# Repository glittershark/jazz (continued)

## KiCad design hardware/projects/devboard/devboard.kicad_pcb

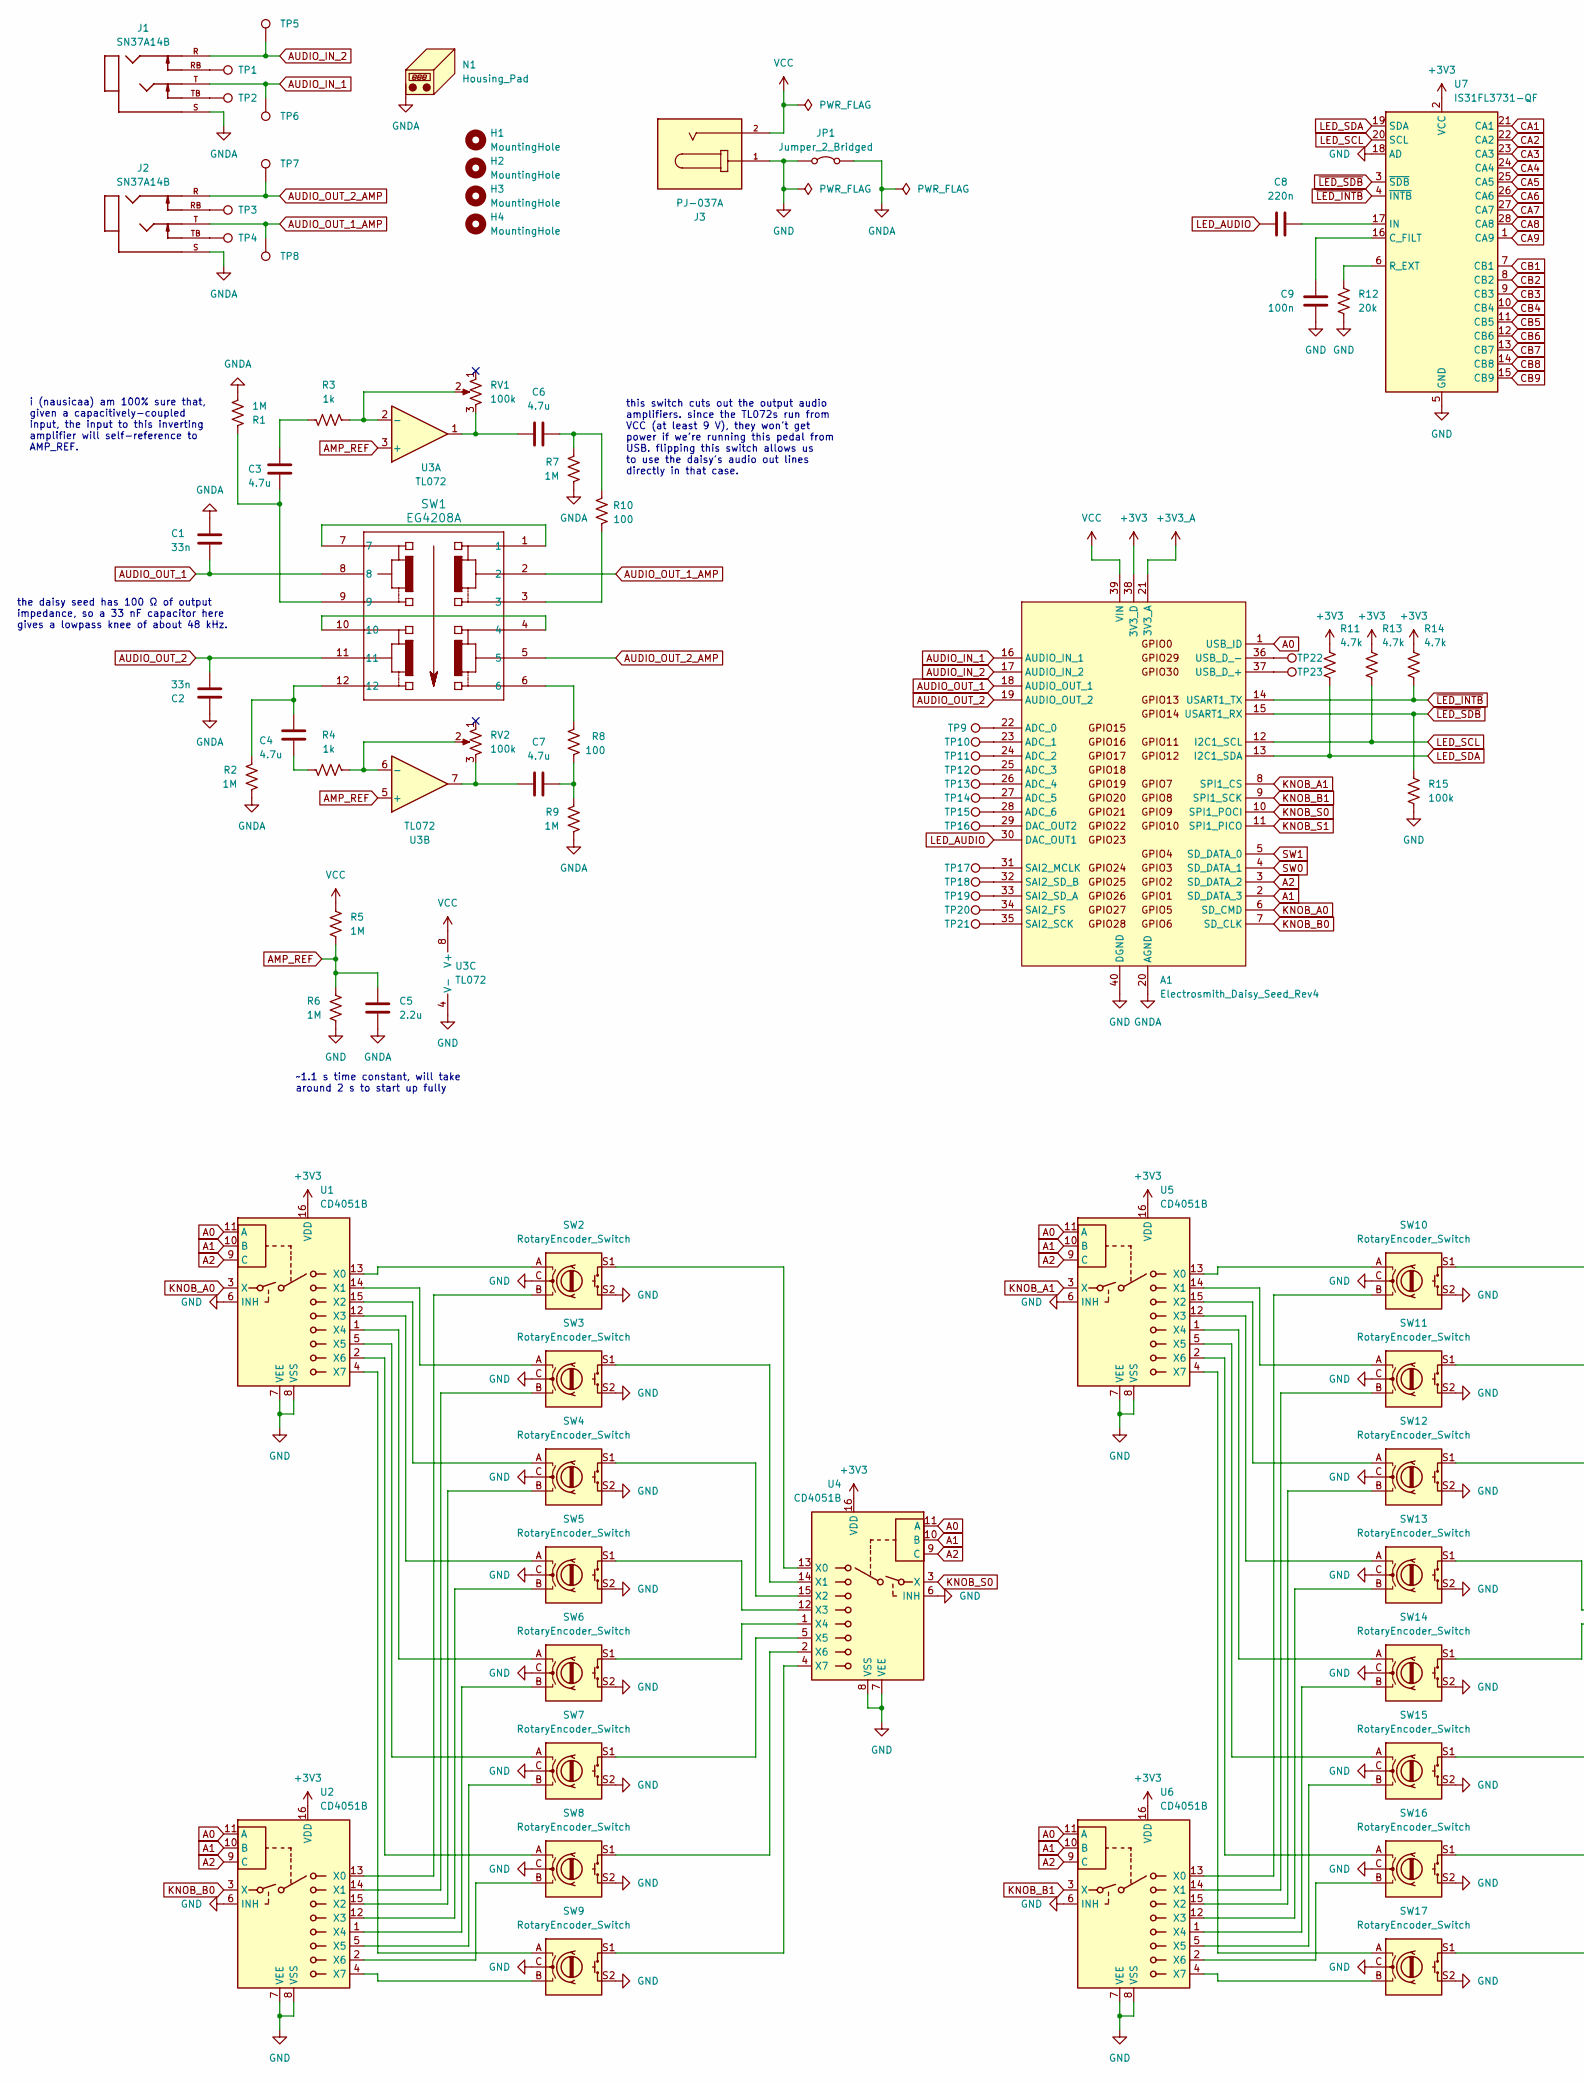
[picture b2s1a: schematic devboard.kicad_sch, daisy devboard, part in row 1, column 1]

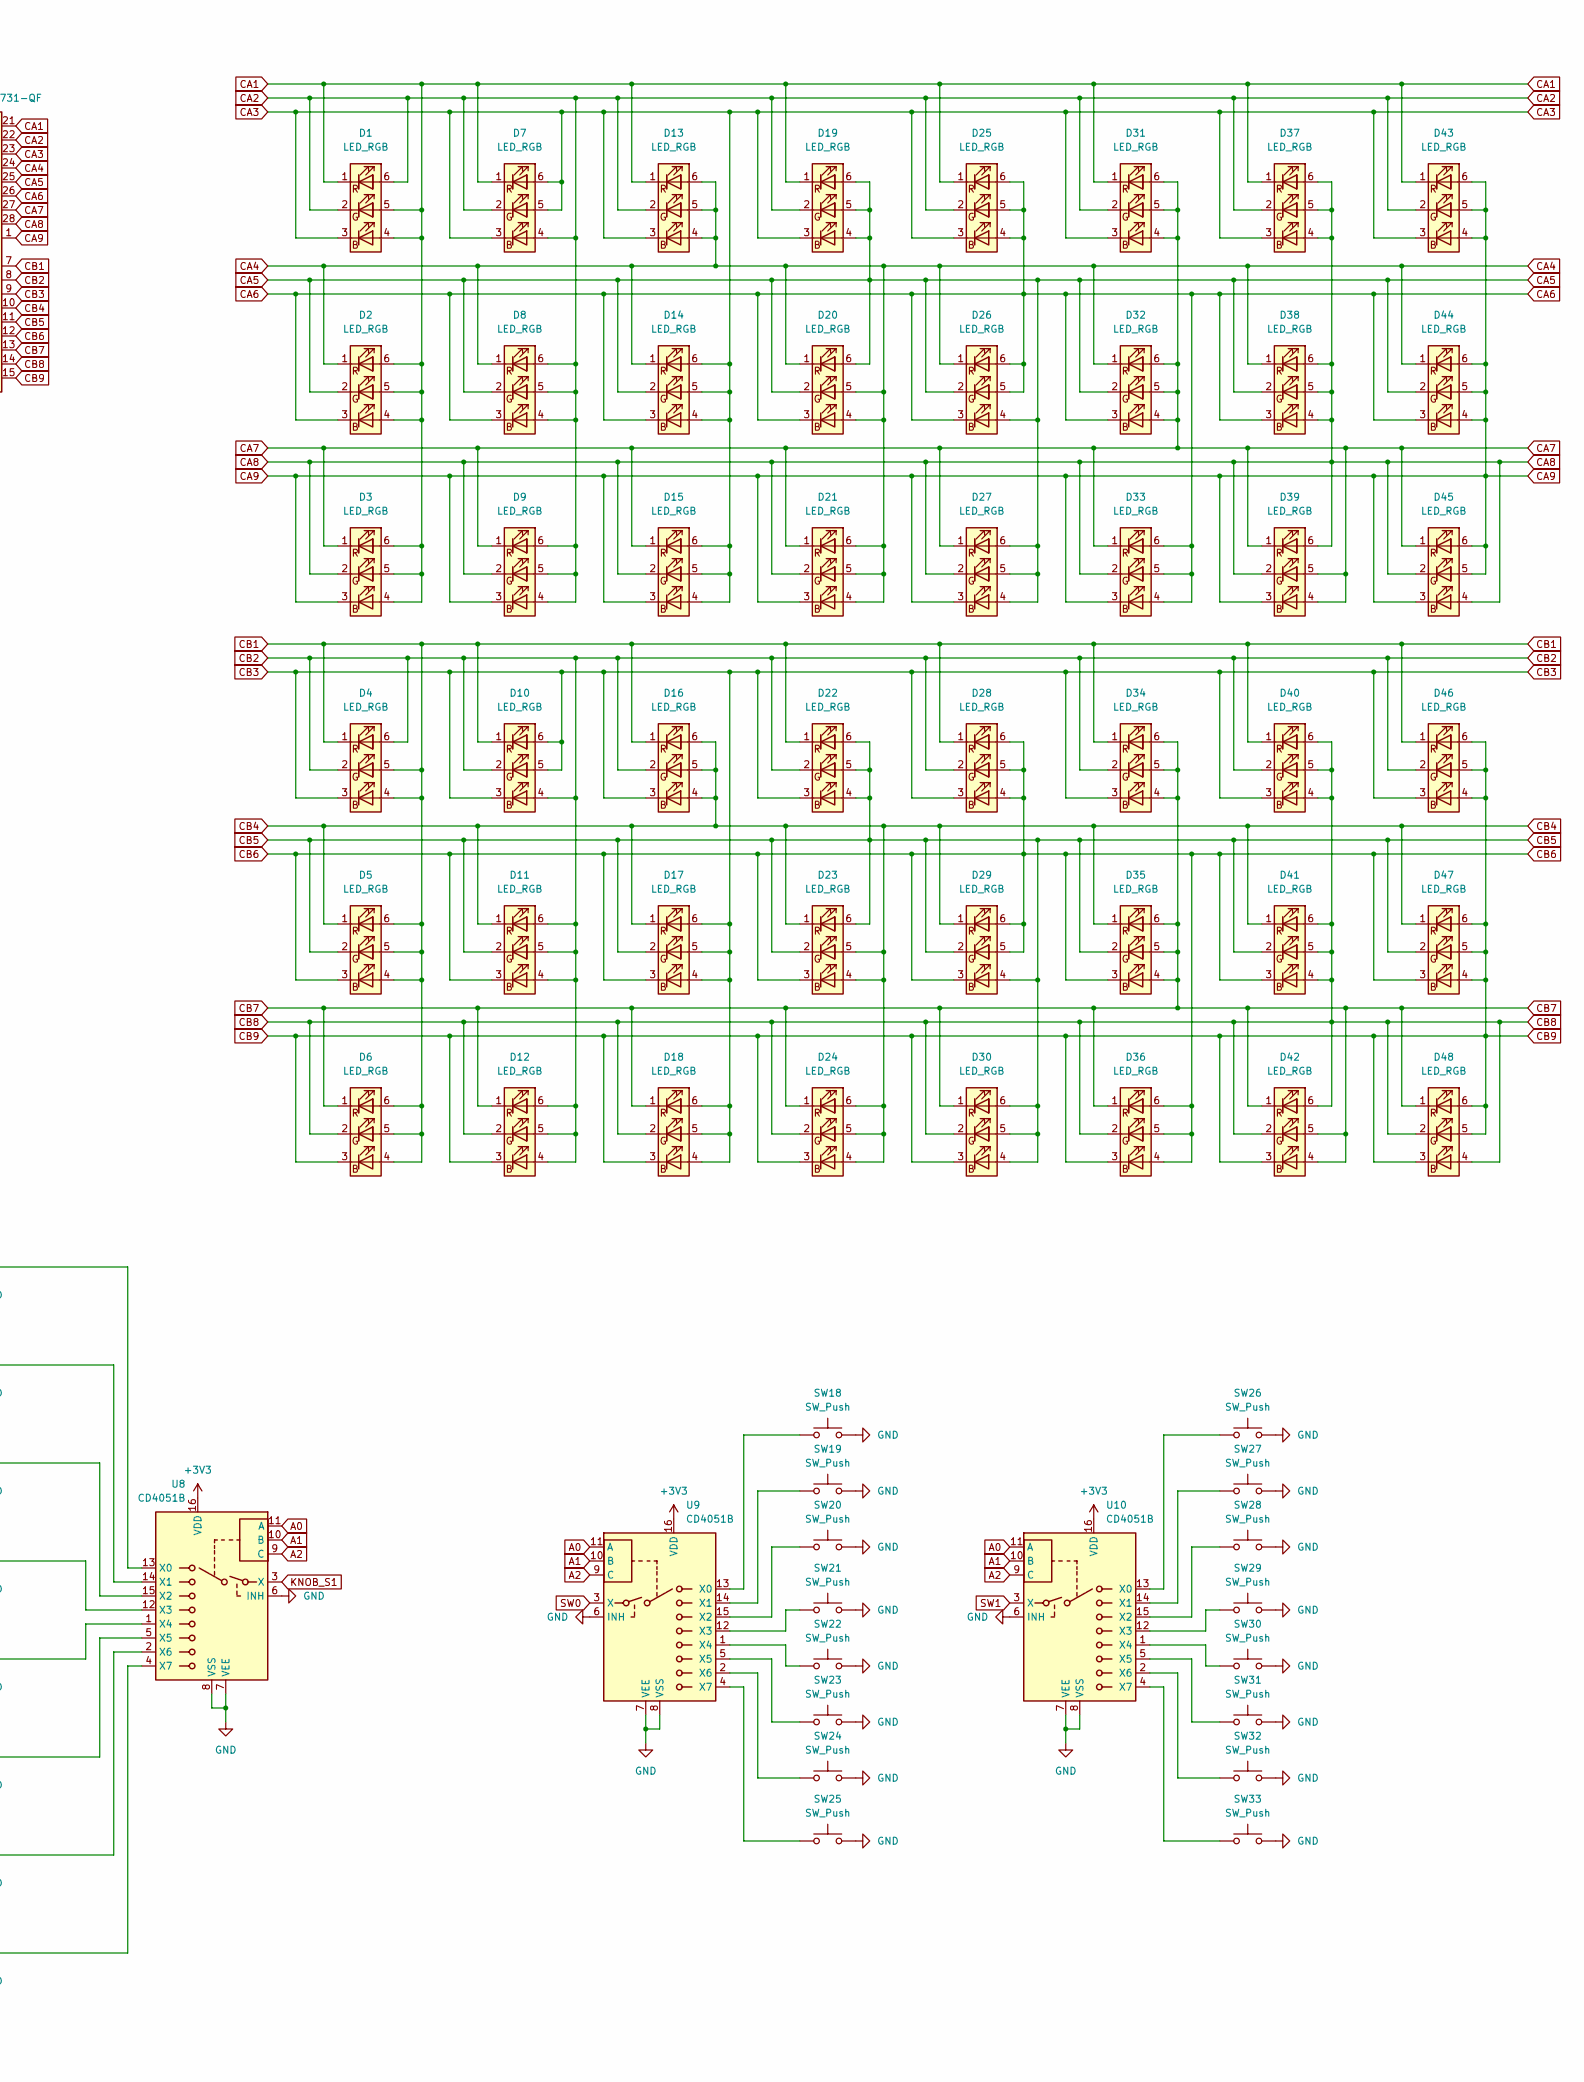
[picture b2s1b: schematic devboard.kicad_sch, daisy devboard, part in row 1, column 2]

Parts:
A1: Electrosmith_Daisy_Seed_Rev4; Electrosmith_Daisy_Seed
C1, C2: 33n; C_0603_1608Metric
C3, C4, C6, C7: 4.7u; C_0603_1608Metric
C5: 2.2u; C_0603_1608Metric
C8: 220n; C_0603_1608Metric
C9: 100n; C_0603_1608Metric
D1, D2, D3, D4, D5, D6, D7, D8, D9, D10, D11, D12, D13, D14, D15, D16, D17, D18, D19, D20, D21, D22, D23, D24, D25, D26, D27, D28, D29, D30, D31, D32, D33, D34, D35, D36, D37, D38, D39, D40, D41, D42, D43, D44, D45, D46, D47, D48: LED_RGB; E6C1615RGBC3UDA-A01
H1, H2, H3, H4: MountingHole; MountingHole_3.2mm_M3
J1, J2: SN37A14B; SWITCHCRAFT_SN37A14B; PARTREV F
J3: PJ-037A; CUI_PJ-037A; PARTREV 1.07
JP1: Jumper_2_Bridged; SolderJumper-2_P1.3mm_Bridged_RoundedPad1.0x1.5mm
N1: Housing_Pad; TestPoint_THTPad_4.0x4.0mm_Drill2.0mm
R1, R2, R5, R6, R7, R9: 1M; R_0603_1608Metric
R3, R4: 1k; R_0603_1608Metric
R8, R10: 100; R_0603_1608Metric
R11, R13, R14: 4.7k; R_0603_1608Metric
R12: 20k; R_0603_1608Metric
R15: 100k; R_0603_1608Metric
RV1, RV2: 100k; Taiss_Potentiometer
SW1: EG4208A; SWITCH12_EG4208A_EWI
SW2, SW3, SW4, SW5, SW6, SW7, SW8, SW9, SW10, SW11, SW12, SW13, SW14, SW15, SW16, SW17: RotaryEncoder_Switch; Encoder_PEC12R-3225F-S0024
SW18, SW19, SW20, SW21, SW22, SW23, SW24, SW25, SW26, SW27, SW28, SW29, SW30, SW31, SW32, SW33: SW_Push; Button_C4B1802110
TP1, TP2, TP3, TP4, TP5, TP6, TP7, TP8, TP9, TP10, TP11, TP12, TP13, TP14, TP15, TP16, TP17, TP18, TP19, TP20, TP21, TP22, TP23: TestPoint; TestPoint_Pad_1.0x1.0mm
U1, U2, U4, U5, U6, U8, U9, U10: CD4051B; SOIC-16_3.9x9.9mm_P1.27mm
U3: TL072; SO-8_3.9x4.9mm_P1.27mm
U7: IS31FL3731-QF; QFN-28-1EP_4x4mm_P0.4mm_EP2.3x2.3mm

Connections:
+3V3: A1.38 (3V3_D), R11.1, R13.1, R14.1, U1.16 (VDD), U2.16 (VDD), U4.16 (VDD), U5.16 (VDD), U6.16 (VDD), U7.2 (VCC), U8.16 (VDD), U9.16 (VDD), U10.16 (VDD)
+3V3_A: A1.21 (3V3_A)
A0: A1.1 (USB_ID), U1.11 (A), U2.11 (A), U4.11 (A), U5.11 (A), U6.11 (A), U8.11 (A), U9.11 (A), U10.11 (A)
A1: A1.2 (SD_DATA_3), U1.10 (B), U2.10 (B), U4.10 (B), U5.10 (B), U6.10 (B), U8.10 (B), U9.10 (B), U10.10 (B)
A2: A1.3 (SD_DATA_2), U1.9 (C), U2.9 (C), U4.9 (C), U5.9 (C), U6.9 (C), U8.9 (C), U9.9 (C), U10.9 (C)
AMP_REF: C5.2, R5.1, R6.2, U3.3 (+), U3.5 (+)
AUDIO_IN_1: A1.16 (AUDIO_IN_1), J1.T, TP6.1 (1_1)
AUDIO_IN_2: A1.17 (AUDIO_IN_2), J1.R, TP5.1 (1_1)
AUDIO_OUT_1: A1.18 (AUDIO_OUT_1), C1.2, SW1.8
AUDIO_OUT_1_AMP: J2.T, SW1.2, TP8.1 (1_1)
AUDIO_OUT_2: A1.19 (AUDIO_OUT_2), C2.2, SW1.11
AUDIO_OUT_2_AMP: J2.R, SW1.5, TP7.1 (1_1)
CA1: D1.1 (RK), D1.4 (BA), D1.5 (GA), D2.4 (BA), D2.5 (GA), D2.6 (RA), D3.4 (BA), D3.5 (GA), D3.6 (RA), D7.1 (RK), D13.1 (RK), D19.1 (RK), D25.1 (RK), D31.1 (RK), D37.1 (RK), D43.1 (RK), U7.21 (CA1)
CA2: D1.2 (GK), D1.6 (RA), D7.2 (GK), D7.4 (BA), D8.4 (BA), D8.5 (GA), D8.6 (RA), D9.4 (BA), D9.5 (GA), D9.6 (RA), D13.2 (GK), D19.2 (GK), D25.2 (GK), D31.2 (GK), D37.2 (GK), D43.2 (GK), U7.22 (CA2)
CA3: D1.3 (BK), D7.3 (BK), D7.5 (GA), D7.6 (RA), D13.3 (BK), D14.4 (BA), D14.5 (GA), D14.6 (RA), D15.4 (BA), D15.5 (GA), D15.6 (RA), D19.3 (BK), D25.3 (BK), D31.3 (BK), D37.3 (BK), D43.3 (BK), U7.23 (CA3)
CA4: D2.1 (RK), D8.1 (RK), D13.4 (BA), D13.5 (GA), D13.6 (RA), D14.1 (RK), D20.1 (RK), D20.4 (BA), D20.5 (GA), D21.4 (BA), D21.5 (GA), D21.6 (RA), D26.1 (RK), D32.1 (RK), D38.1 (RK), D44.1 (RK), U7.24 (CA4)
CA5: D2.2 (GK), D8.2 (GK), D14.2 (GK), D19.4 (BA), D19.5 (GA), D19.6 (RA), D20.2 (GK), D20.6 (RA), D26.2 (GK), D26.4 (BA), D27.4 (BA), D27.5 (GA), D27.6 (RA), D32.2 (GK), D38.2 (GK), D44.2 (GK), U7.25 (CA5)
CA6: D2.3 (BK), D8.3 (BK), D14.3 (BK), D20.3 (BK), D25.4 (BA), D25.5 (GA), D25.6 (RA), D26.3 (BK), D26.5 (GA), D26.6 (RA), D32.3 (BK), D33.4 (BA), D33.5 (GA), D33.6 (RA), D38.3 (BK), D44.3 (BK), U7.26 (CA6)
CA7: D3.1 (RK), D9.1 (RK), D15.1 (RK), D21.1 (RK), D27.1 (RK), D31.4 (BA), D31.5 (GA), D31.6 (RA), D32.4 (BA), D32.5 (GA), D32.6 (RA), D33.1 (RK), D39.1 (RK), D39.4 (BA), D39.5 (GA), D45.1 (RK), U7.27 (CA7)
CA8: D3.2 (GK), D9.2 (GK), D15.2 (GK), D21.2 (GK), D27.2 (GK), D33.2 (GK), D37.4 (BA), D37.5 (GA), D37.6 (RA), D38.4 (BA), D38.5 (GA), D38.6 (RA), D39.2 (GK), D39.6 (RA), D45.2 (GK), D45.4 (BA), U7.28 (CA8)
CA9: D3.3 (BK), D9.3 (BK), D15.3 (BK), D21.3 (BK), D27.3 (BK), D33.3 (BK), D39.3 (BK), D43.4 (BA), D43.5 (GA), D43.6 (RA), D44.4 (BA), D44.5 (GA), D44.6 (RA), D45.3 (BK), D45.5 (GA), D45.6 (RA), U7.1 (CA9)
CB1: D4.1 (RK), D4.4 (BA), D4.5 (GA), D5.4 (BA), D5.5 (GA), D5.6 (RA), D6.4 (BA), D6.5 (GA), D6.6 (RA), D10.1 (RK), D16.1 (RK), D22.1 (RK), D28.1 (RK), D34.1 (RK), D40.1 (RK), D46.1 (RK), U7.7 (CB1)
CB2: D4.2 (GK), D4.6 (RA), D10.2 (GK), D10.4 (BA), D11.4 (BA), D11.5 (GA), D11.6 (RA), D12.4 (BA), D12.5 (GA), D12.6 (RA), D16.2 (GK), D22.2 (GK), D28.2 (GK), D34.2 (GK), D40.2 (GK), D46.2 (GK), U7.8 (CB2)
CB3: D4.3 (BK), D10.3 (BK), D10.5 (GA), D10.6 (RA), D16.3 (BK), D17.4 (BA), D17.5 (GA), D17.6 (RA), D18.4 (BA), D18.5 (GA), D18.6 (RA), D22.3 (BK), D28.3 (BK), D34.3 (BK), D40.3 (BK), D46.3 (BK), U7.9 (CB3)
CB4: D5.1 (RK), D11.1 (RK), D16.4 (BA), D16.5 (GA), D16.6 (RA), D17.1 (RK), D23.1 (RK), D23.4 (BA), D23.5 (GA), D24.4 (BA), D24.5 (GA), D24.6 (RA), D29.1 (RK), D35.1 (RK), D41.1 (RK), D47.1 (RK), U7.10 (CB4)
CB5: D5.2 (GK), D11.2 (GK), D17.2 (GK), D22.4 (BA), D22.5 (GA), D22.6 (RA), D23.2 (GK), D23.6 (RA), D29.2 (GK), D29.4 (BA), D30.4 (BA), D30.5 (GA), D30.6 (RA), D35.2 (GK), D41.2 (GK), D47.2 (GK), U7.11 (CB5)
CB6: D5.3 (BK), D11.3 (BK), D17.3 (BK), D23.3 (BK), D28.4 (BA), D28.5 (GA), D28.6 (RA), D29.3 (BK), D29.5 (GA), D29.6 (RA), D35.3 (BK), D36.4 (BA), D36.5 (GA), D36.6 (RA), D41.3 (BK), D47.3 (BK), U7.12 (CB6)
CB7: D6.1 (RK), D12.1 (RK), D18.1 (RK), D24.1 (RK), D30.1 (RK), D34.4 (BA), D34.5 (GA), D34.6 (RA), D35.4 (BA), D35.5 (GA), D35.6 (RA), D36.1 (RK), D42.1 (RK), D42.4 (BA), D42.5 (GA), D48.1 (RK), U7.13 (CB7)
CB8: D6.2 (GK), D12.2 (GK), D18.2 (GK), D24.2 (GK), D30.2 (GK), D36.2 (GK), D40.4 (BA), D40.5 (GA), D40.6 (RA), D41.4 (BA), D41.5 (GA), D41.6 (RA), D42.2 (GK), D42.6 (RA), D48.2 (GK), D48.4 (BA), U7.14 (CB8)
CB9: D6.3 (BK), D12.3 (BK), D18.3 (BK), D24.3 (BK), D30.3 (BK), D36.3 (BK), D42.3 (BK), D46.4 (BA), D46.5 (GA), D46.6 (RA), D47.4 (BA), D47.5 (GA), D47.6 (RA), D48.3 (BK), D48.5 (GA), D48.6 (RA), U7.15 (CB9)
GND: A1.40 (DGND), C9.2, J3.1, JP1.1 (A), R6.1, R12.2, R15.2, SW2.C, SW2.S2, SW3.C, SW3.S2, SW4.C, SW4.S2, SW5.C, SW5.S2, SW6.C, SW6.S2, SW7.C, SW7.S2, SW8.C, SW8.S2, SW9.C, SW9.S2, SW10.C, SW10.S2, SW11.C, SW11.S2, SW12.C, SW12.S2, SW13.C, SW13.S2, SW14.C, SW14.S2, SW15.C, SW15.S2, SW16.C, SW16.S2, SW17.C, SW17.S2, SW18.2, SW19.2, SW20.2, SW21.2, SW22.2, SW23.2, SW24.2, SW25.2, SW26.2, SW27.2, SW28.2, SW29.2, SW30.2, SW31.2, SW32.2, SW33.2, U1.6 (INH), U1.7 (VEE), U1.8 (VSS), U2.6 (INH), U2.7 (VEE), U2.8 (VSS), U3.4 (V-), U4.6 (INH), U4.7 (VEE), U4.8 (VSS), U5.6 (INH), U5.7 (VEE), U5.8 (VSS), U6.6 (INH), U6.7 (VEE), U6.8 (VSS), U7.5 (GND), U7.18 (AD), U7.29 (GND), U8.6 (INH), U8.7 (VEE), U8.8 (VSS), U9.6 (INH), U9.7 (VEE), U9.8 (VSS), U10.6 (INH), U10.7 (VEE), U10.8 (VSS)
GNDA: A1.20 (AGND), C1.1, C2.1, C5.1, J1.S, J2.S, JP1.2 (B), N1.1 (PAD_1), R1.2, R2.2, R7.2, R9.2
KNOB_A0: A1.6 (SD_CMD), U1.3 (X)
KNOB_A1: A1.8 (SPI1_CS), U5.3 (X)
KNOB_B0: A1.7 (SD_CLK), U2.3 (X)
KNOB_B1: A1.9 (SPI1_SCK), U6.3 (X)
KNOB_S0: A1.10 (SPI1_POCI), U4.3 (X)
KNOB_S1: A1.11 (SPI1_PICO), U8.3 (X)
LED_AUDIO: A1.30 (DAC_OUT1), C8.1
LED_SCL: A1.12 (I2C1_SCL), R13.2, U7.20 (SCL)
LED_SDA: A1.13 (I2C1_SDA), R11.2, U7.19 (SDA)
unnamed: A1.22 (ADC_0), TP9.1 (1_1)
unnamed: A1.23 (ADC_1), TP10.1 (1_1)
unnamed: A1.24 (ADC_2), TP11.1 (1_1)
unnamed: A1.25 (ADC_3), TP12.1 (1_1)
unnamed: A1.26 (ADC_4), TP13.1 (1_1)
unnamed: A1.27 (ADC_5), TP14.1 (1_1)
unnamed: A1.28 (ADC_6), TP15.1 (1_1)
unnamed: A1.29 (DAC_OUT2), TP16.1 (1_1)
unnamed: A1.34 (SAI2_FS), TP20.1 (1_1)
unnamed: A1.31 (SAI2_MCLK), TP17.1 (1_1)
unnamed: A1.35 (SAI2_SCK), TP21.1 (1_1)
unnamed: A1.33 (SAI2_SD_A), TP19.1 (1_1)
unnamed: A1.32 (SAI2_SD_B), TP18.1 (1_1)
unnamed: A1.37 (USB_D_+), TP23.1 (1_1)
unnamed: A1.36 (USB_D_-), TP22.1 (1_1)
unnamed: C3.1, R3.2
unnamed: C3.2, R1.1, SW1.9
unnamed: C4.1, R2.1, SW1.12
unnamed: C4.2, R4.2
unnamed: C6.1, R7.1, R10.1
unnamed: C6.2, RV1.3, U3.1
unnamed: C7.1, R8.2, R9.1
unnamed: C7.2, RV2.3, U3.7
unnamed: J1.RB, TP1.1 (1_1)
unnamed: J1.TB, TP2.1 (1_1)
unnamed: J2.RB, TP3.1 (1_1)
unnamed: J2.TB, TP4.1 (1_1)
unnamed: R8.1, SW1.6
unnamed: R10.2, SW1.3
unnamed: SW1.1, SW1.7
unnamed: SW1.4, SW1.10
unnamed: SW2.A, U1.13 (X0)
unnamed: SW3.A, U1.14 (X1)
unnamed: SW4.A, U1.15 (X2)
unnamed: SW5.A, U1.12 (X3)
unnamed: SW6.A, U1.1 (X4)
unnamed: SW7.A, U1.5 (X5)
unnamed: SW8.A, U1.2 (X6)
unnamed: SW9.A, U1.4 (X7)
unnamed: SW2.B, U2.13 (X0)
unnamed: SW3.B, U2.14 (X1)
unnamed: SW4.B, U2.15 (X2)
unnamed: SW5.B, U2.12 (X3)
unnamed: SW6.B, U2.1 (X4)
unnamed: SW7.B, U2.5 (X5)
unnamed: SW8.B, U2.2 (X6)
unnamed: SW9.B, U2.4 (X7)
unnamed: R3.1, RV1.2, U3.2 (-)
unnamed: R4.1, RV2.2, U3.6 (-)
unnamed: SW2.S1, U4.13 (X0)
unnamed: SW3.S1, U4.14 (X1)
unnamed: SW4.S1, U4.15 (X2)
unnamed: SW5.S1, U4.12 (X3)
unnamed: SW6.S1, U4.1 (X4)
unnamed: SW7.S1, U4.5 (X5)
unnamed: SW8.S1, U4.2 (X6)
unnamed: SW9.S1, U4.4 (X7)
unnamed: SW10.A, U5.13 (X0)
unnamed: SW11.A, U5.14 (X1)
unnamed: SW12.A, U5.15 (X2)
unnamed: SW13.A, U5.12 (X3)
unnamed: SW14.A, U5.1 (X4)
unnamed: SW15.A, U5.5 (X5)
unnamed: SW16.A, U5.2 (X6)
unnamed: SW17.A, U5.4 (X7)
unnamed: SW10.B, U6.13 (X0)
unnamed: SW11.B, U6.14 (X1)
unnamed: SW12.B, U6.15 (X2)
unnamed: SW13.B, U6.12 (X3)
unnamed: SW14.B, U6.1 (X4)
unnamed: SW15.B, U6.5 (X5)
unnamed: SW16.B, U6.2 (X6)
unnamed: SW17.B, U6.4 (X7)
unnamed: C9.1, U7.16 (C_FILT)
unnamed: C8.2, U7.17 (IN)
unnamed: R12.1, U7.6 (R_EXT)
unnamed: SW10.S1, U8.13 (X0)
unnamed: SW11.S1, U8.14 (X1)
unnamed: SW12.S1, U8.15 (X2)
unnamed: SW13.S1, U8.12 (X3)
unnamed: SW14.S1, U8.1 (X4)
unnamed: SW15.S1, U8.5 (X5)
unnamed: SW16.S1, U8.2 (X6)
unnamed: SW17.S1, U8.4 (X7)
unnamed: SW18.1, U9.13 (X0)
unnamed: SW19.1, U9.14 (X1)
unnamed: SW20.1, U9.15 (X2)
unnamed: SW21.1, U9.12 (X3)
unnamed: SW22.1, U9.1 (X4)
unnamed: SW23.1, U9.5 (X5)
unnamed: SW24.1, U9.2 (X6)
unnamed: SW25.1, U9.4 (X7)
unnamed: SW26.1, U10.13 (X0)
unnamed: SW27.1, U10.14 (X1)
unnamed: SW28.1, U10.15 (X2)
unnamed: SW29.1, U10.12 (X3)
unnamed: SW30.1, U10.1 (X4)
unnamed: SW31.1, U10.5 (X5)
unnamed: SW32.1, U10.2 (X6)
unnamed: SW33.1, U10.4 (X7)
SW0: A1.4 (SD_DATA_1), U9.3 (X)
SW1: A1.5 (SD_DATA_0), U10.3 (X)
VCC: A1.39 (VIN), J3.2, R5.2, U3.8 (V+)
~LED_INTB: A1.14 (USART1_TX), R14.2, U7.4 (~INTB)
~LED_SDB: A1.15 (USART1_RX), R15.1, U7.3 (~SDB)

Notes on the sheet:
the daisy seed has 100 Ω of output impedance, so a 33 nF capacitor here gives a lowpass knee of about 48 kHz.
this switch cuts out the output audio amplifiers. since the TL072s run from VCC (at least 9 V), they won't get power if we're running this pedal from USB. flipping this switch allows us to use the daisy's audio out lines directly in that case.
i (nausicaa) am 100% sure that, given a capacitively-coupled input, the input to this inverting amplifier will self-reference to AMP_REF.
~1.1 s time constant, will take around 2 s to start up fully

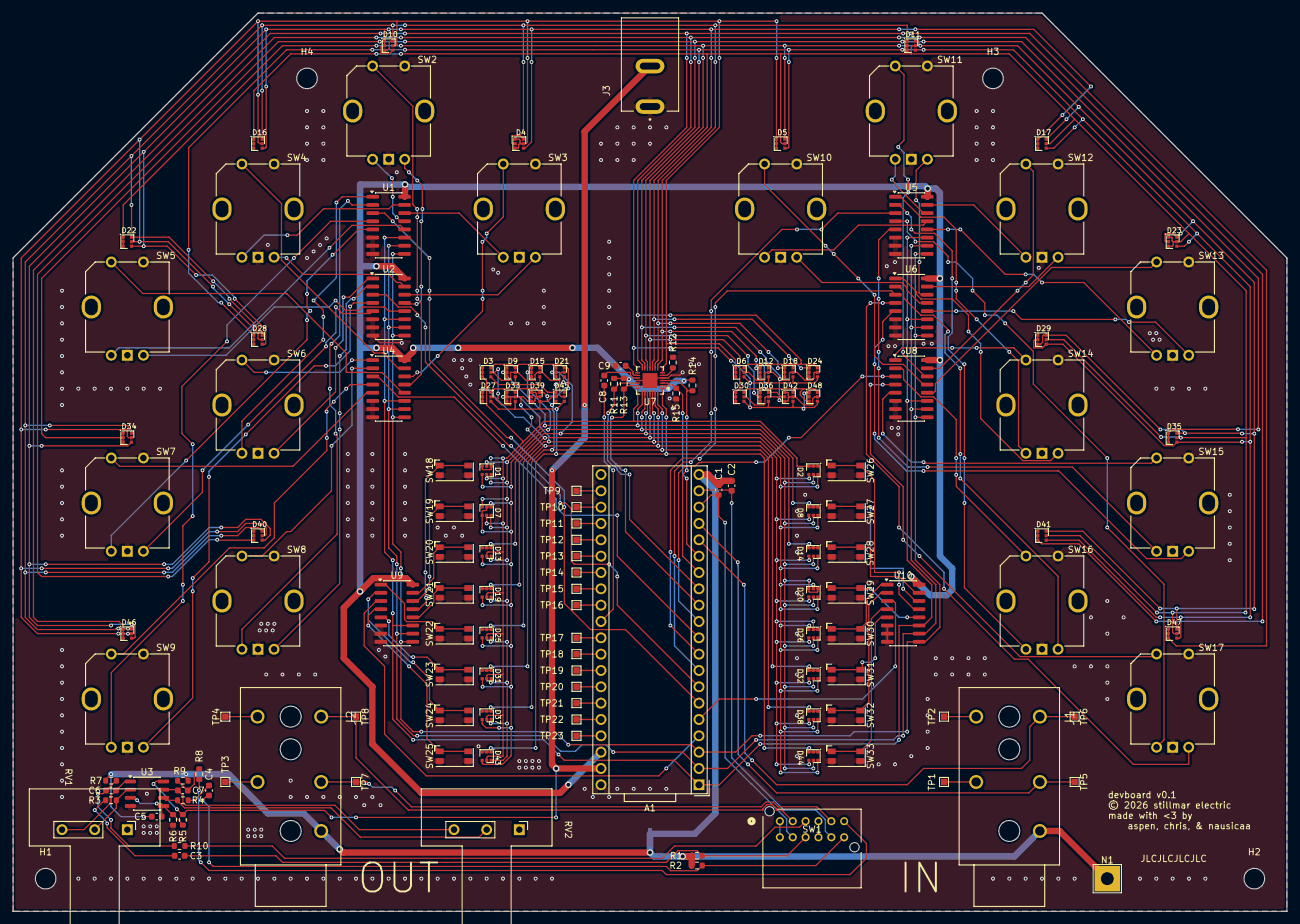
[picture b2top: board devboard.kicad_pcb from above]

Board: 2 copper layers, 198.1 x 139.7 mm, 150 parts (1 on the bottom side), 145 nets.

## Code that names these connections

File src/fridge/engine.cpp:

#include "engine.hpp"

#include <cstddef>

#include "callback.hpp"
#include "config.hpp"
#include "libjazz/units.hpp"

#ifndef UNIT_TEST

#include "daisy_seed.h"
#include "io.hpp"

using namespace jazz;
using namespace daisy;
using namespace daisy::seed;
using namespace fridge;
using namespace fridge::engine;
using jazz::units::Samples;

Timer::Timer(daisy::TimerHandle::Config::Peripheral timer, Callback<> callback,
             std::chrono::microseconds period)
    : callback_(callback), period_(period) {
  daisy::TimerHandle::Config timer_config;
  timer_config.periph = timer;
  timer_config.enable_irq = true;

  timer_.Init(timer_config);
  timer_.SetCallback(Timer::timer_callback_, this);
  timer_.SetPeriod((period_.count() * timer_.GetFreq()) / 1'000'000);
}

namespace {
constexpr const size_t kSW0 = 0;
constexpr const size_t kSW1 = 1;
constexpr const size_t kKNOB_A0 = 2;
constexpr const size_t kKNOB_B0 = 3;
constexpr const size_t kKNOB_A1 = 4;
constexpr const size_t kKNOB_B1 = 5;
constexpr const size_t kKNOB_S0 = 6;
constexpr const size_t kKNOB_S1 = 7;

enum class KnobBank { K0, K1 };

static size_t knob_a(KnobBank bank) {
  switch (bank) {
  case KnobBank::K0:
    return kKNOB_A0;
  case KnobBank::K1:
    return kKNOB_A1;
  default:
    assert(false);
  }
}

static size_t knob_b(KnobBank bank) {
  switch (bank) {
  case KnobBank::K0:
    return kKNOB_B0;
  case KnobBank::K1:
    return kKNOB_B1;
  default:
    assert(false);
  }
}

static size_t knob_s(KnobBank bank) {
  switch (bank) {
  case KnobBank::K0:
    return kKNOB_S0;
  case KnobBank::K1:
    return kKNOB_S1;
  default:
    assert(false);
  }
}

static io::PushbuttonQuadratureEncoder knob(
    io::mux::MultiGpioInMux<Engine::kMuxes>* mux, KnobBank bank,
    size_t channel) {
  return io::PushbuttonQuadratureEncoder({
      .a = mux->channel(knob_a(bank), channel),
      .b = mux->channel(knob_b(bank), channel),
      .button = mux->channel(knob_s(bank), channel),
  });
}
}  // namespace

Engine::Engine(config::Config initial_config)
    // TODO: assign the right pins in here
    : mux_({
          /* 0 =*/io::mux::GpioInMux(D3),   // SW0 in the schematic
          /* 1 =*/io::mux::GpioInMux(D4),   // SW1 in the schematic
          /* 2 =*/io::mux::GpioInMux(D5),   // KNOB_A0 in the schematic
          /* 3 =*/io::mux::GpioInMux(D6),   // KNOB_B0 in the schematic
          /* 4 =*/io::mux::GpioInMux(D7),   // KNOB_A1 in the schematic
          /* 5 =*/io::mux::GpioInMux(D8),   // KNOB_B1 in the schematic
          /* 6 =*/io::mux::GpioInMux(D9),   // KNOB_S0 in the schematic
          /* 7 =*/io::mux::GpioInMux(D10),  // KNOB_S1 in the schematic
      }),

      scan_(io::mux::Address(D0, D1, D2), &mux_),

      timer_(TimerHandle::Config::Peripheral::TIM_3, scan_.GetCallback()),

      // dry = SW2
      dry_(knob(&mux_, KnobBank::K0, 1)),
      // wet = SW3
      wet_(knob(&mux_, KnobBank::K0, 0)),

      head_{// position = SW4
            .position = knob(&mux_, KnobBank::K0, 2),
            // write_amount = SW5
            .write_amount = knob(&mux_, KnobBank::K0, 3),
            // read_amount = SW6
            .read_amount = knob(&mux_, KnobBank::K0, 4),
            // erase_amount = Sw7
            .erase_amount = knob(&mux_, KnobBank::K0, 5),
            // feedback = SW8
            .feedback = knob(&mux_, KnobBank::K0, 6),
            // pan = SW9
            .pan = knob(&mux_, KnobBank::K0, 7)},

      lfo_{
          // max_grain_size = SW11
          .max_grain_size = knob(&mux_, KnobBank::K1, 1),
          // min_grain_size = SW12
          .min_grain_size = knob(&mux_, KnobBank::K1, 2),
          // reverse_chance = SW13
          .reverse_chance = knob(&mux_, KnobBank::K1, 3),
          // teleport_chance = SW14
          .teleport_chance = knob(&mux_, KnobBank::K1, 4),
          // pitch_shift_chance = SW15
          .pitch_shift_chance = knob(&mux_, KnobBank::K1, 5),
          // low_octave_chance = SW16
          .low_octave_chance = knob(&mux_, KnobBank::K1, 6),
          // high_octave_chance = SW17
          .high_octave_chance = knob(&mux_, KnobBank::K1, 7),
      },

      // range = SW10, now owned by the assigned region
      range_(knob(&mux_, KnobBank::K1, 0)),

      // Ten head/LFO pairs: SW0 followed by the first two SW1 buttons
      head_select_{
          mux_.channel(kSW0, 0), mux_.channel(kSW0, 1), mux_.channel(kSW0, 2),
          mux_.channel(kSW0, 3), mux_.channel(kSW0, 4), mux_.channel(kSW0, 5),
          mux_.channel(kSW0, 6), mux_.channel(kSW0, 7), mux_.channel(kSW1, 0),
          mux_.channel(kSW1, 1),
      },

      // The remaining six SW1 buttons assign the selected pair's region.
      region_select_{
          mux_.channel(kSW1, 2), mux_.channel(kSW1, 3), mux_.channel(kSW1, 4),
          mux_.channel(kSW1, 5), mux_.channel(kSW1, 6), mux_.channel(kSW1, 7),
      },

      config_(initial_config),

      leds_({
          .interrupt = D13,
          .shutdown = D14,

      }),

      ui_(leds_, &config_) {
  modulator_.SetConfig(config_.Read());
  // assign physical controls to UI controls

  head_.position.OnChange(ui_.head_knobs().position.GetCallback());
  head_.write_amount.OnChange(ui_.head_knobs().write_amount.GetCallback());
  head_.read_amount.OnChange(ui_.head_knobs().read_amount.GetCallback());
  head_.erase_amount.OnChange(ui_.head_knobs().erase_amount.GetCallback());
  head_.feedback.OnChange(ui_.head_knobs().feedback.GetCallback());
  head_.pan.OnChange(ui_.head_knobs().pan.GetCallback());

  dry_.OnChange(ui_.dry_knob().GetCallback());
  wet_.OnChange(ui_.wet_knob().GetCallback());

  range_.OnChange(ui_.range_knob().GetCallback());
  lfo_.max_grain_size.OnChange(ui_.lfo_knobs().max_grain_size.GetCallback());
  lfo_.min_grain_size.OnChange(ui_.lfo_knobs().min_grain_size.GetCallback());
  lfo_.reverse_chance.OnChange(ui_.lfo_knobs().reverse_chance.GetCallback());
  lfo_.teleport_chance.OnChange(ui_.lfo_knobs().teleport_chance.GetCallback());
  lfo_.pitch_shift_chance.OnChange(
      ui_.lfo_knobs().pitch_shift_chance.GetCallback());
  lfo_.low_octave_chance.OnChange(
      ui_.lfo_knobs().low_octave_chance.GetCallback());
  lfo_.high_octave_chance.OnChange(
      ui_.lfo_knobs().high_octave_chance.GetCallback());

  // and then physical buttons (registers in the order you would expect)
  ui_.head_select().RegisterCallbacks(head_select_);
  ui_.region_select().RegisterCallbacks(region_select_);

  // TODO: tempo button should probably be connected to something lol

  timer_.Start();
}

void Engine::SyncConfig() {
  if (!config_.dirty()) {
    return;
  }

  // The scan IRQ writes the config and the audio IRQ walks the modulator's
  // state; don't let either observe a half-applied swap.
  __disable_irq();
  config_.MarkClean();
  modulator_.SetConfig(config_.Read());
  __enable_irq();
}

#endif  // UNIT_TEST

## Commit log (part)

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2026-03-12 fridge: Fix attribute names in feedback
2026-03-12 Add initial CI config
2026-03-15 Add host audio CLI for granular processing
2026-03-19 Improve host CLI and add selectable effects
2026-03-19 fridge: (untested) GPIO mux and quadrature encoders
    Probably it's fine?
2026-03-19 Add effect chains, params, and presets to host CLI
2026-03-26 voidarameter
2026-03-26 Add doc for encoder
2026-03-26 Add host audio CLI for granular processing (#2)
    ## Summary
    - add a host-side `jazz-console` CLI for MP3 decode/process/play/export
    using ffmpeg/ffplay
    - wire console into TEST_ONLY CMake and add `BUILD_TESTS` toggle
    - add `make console` and README usage for host iteration
    - fix granular host-build issues required to link the CLI
2026-03-28 fridge: Just pass a Pin to GpioInMux
2026-03-28 fridge: a working quadrature encoder!
2026-03-28 fridge: Datasheet for the LED
2026-03-28 ongoing work
2026-03-28 fridge: Refactor GPIO mux, allow parallel muxen
    The general idea here is to split out the "scan over the channels" bit
    from the "record the current state of each channel, with callbacks" bit.
    This allows multiple muxen, for example, to share the A/B/C channel pins,
    which is useful for quadrature encoders (two pins) or RGB LEDs (three
    pins).
    The current main implementation has a working demo of two encoders going
2026-04-04 RGB LED via PWM
2026-04-04 notes for the guy
2026-04-05 fridge: Fix build + tests
2026-04-05 fridge: Use cc and h instead of cpp and hpp
2026-04-05 fridge: Split color out into its own file
2026-04-05 Check clang-format in CI
2026-04-05 Fix a bunch of clang-tidy lints
    But, sadly, don't run it in CI yet, because there are some build-env
    issues that prevent it from fully passing
2026-04-05 Fridge: Split up into multiple files
2026-04-09 fridge: split out constants.hpp from config
2026-04-09 fridge: getters for Config
2026-04-09 Drop tracked build artifacts from branch
2026-04-09 Stop tracking mp3 assets
2026-04-09 fridge: Port over sound + refactor from granular
    The main public-facing API here is a Sound class, which most importantly
    just has a ProcessSample method, which takes a reference to the current
    Config (as being updated live by state) and a sample, and returns a new
    sample.
2026-04-09 fridge: Actually define the slabs for sound
2026-04-09 fridge: Sound takes config as const
2026-04-09 Refactor fridge config transform module
2026-04-09 Refine fridge config transform state model
2026-04-09 Refine fridge transform module structure
2026-04-09 format deez
2026-04-09 Convert fridge config to plain data structs
2026-04-09 Convert fridge config to plain data structs (#4)
    deez
2026-04-09 Draft UI structure
    This also makes some ergonomic changes elsewhere in the code, and
    functional changes to QuadratureEncoder (it no longer stores state).
2026-04-09 Fail a test on an unfinished function (but compile!)
2026-04-11 fridge/ui: cover most things in tests
2026-04-12 fridge/ui: pass tests finally lol
2026-04-12 start led controller
2026-04-12 make
2026-04-16 Fix some clang-tidy lints
2026-04-16 Include the linker script in build
    otherwise nothing works lmao
2026-04-16 Build firmware before flashing
2026-04-22 Remove vendor/libDaisy in preparation for subtree merge
2026-04-22 Remove vendor/DaisySP in preparation for subtree
2026-04-22 Remove vendor/stmlib in preparation for subtree
2026-04-22 remove vendor/libDaisy in preparation for a submodule
2026-04-22 add vendor/libDaisy as a submodule
2026-04-22 ci: check out submodules recursively
2026-04-22 main program to test the led
2026-04-22 cache register values
2026-04-22 cycle hue
2026-04-22 fridge/ui: use Set() / Get() for knobs
2026-04-22 try to configure the thing before we use it
2026-04-22 add shutdown controls
2026-04-22 fix comparison in saturating arithmetic
2026-04-22 change default address, don't wait
2026-04-22 Impose the style guide
2026-04-22 enforce c++20 for clangd
2026-04-22 set led intensity with the knobs
    this is slightly broken tho
2026-04-22 fridge/led: draft controller
2026-04-22 switch on LEDs properly
2026-04-22 include led.hpp in io.hpp
2026-04-22 fridge/led: use your verbs
    (i like 'em)
2026-04-22 fridge/led: comment on what the LED functions do
2026-04-22 fridge/led: comment on where the magic came from
2026-04-22 add support for the LED controller (#5)
2026-04-23 Configurable Hue-wheel value display
    With:
    - scaling (eg, not in the hue range 0-255)
    - custom saturation+value
    - gama correction
    This should be pluggable on top of the LED controller to display the
    current value of a knob
2026-04-23 static_cast
2026-04-23 comment that udiff is not very good
2026-04-23 comment about gamma correction
2026-04-23 Configurable Hue-wheel value display (#8)
    With:
    - scaling (eg, not in the hue range 0-255)
    - custom saturation+value
    - gama correction
    This should be pluggable on top of the LED controller to display the
    current value of a knob
2026-04-23 Add an RgbLed class
    This is horrifically simple, but still a modicum nicer than doing things
    manually.
2026-04-23 RgbLedValueDisplay class
    Again, extremely simple, but one notch closer to the concept we want to
    express: tie together a (generic) ValueDisplay and an RgbLed.
2026-04-23 move existing driver code into engine.cpp
2026-04-23 integrate everything into top-level functions
2026-04-23 construct the engine
2026-04-23 construct the actual engine in main()
2026-04-23 respond to PR comments
    <3
2026-04-23 Add fridge terminal demo tooling
2026-04-23 Make fridge LFO motion modular
2026-04-23 Align fridge erase amount semantics
2026-04-23 Document fridge clicking followups
2026-04-23 Integrate the engine (#11)
2026-04-23 construct sound::Sound in .sdram_bss
2026-04-23 Ignore local png assets
2026-04-23 Add head transition fades for LFO jumps
2026-05-07 Linear interpolation in CIE color space for value display
    Including a very pretty blue-to-green gradient
2026-05-07 fix submodule dont make
2026-05-07 Handle zero LFO range explicitly
2026-05-07 Document head transition helpers
2026-05-07 Document head transition recording
2026-05-07 Accumulate LFO transitions across tick
2026-05-07 Return wet head contribution from ApplyHead
2026-05-09 address PR comments
    - use <chrono> for timer period
    - use a static_cast
    - address comments on Timer
    - add some clarity to Engine
    - address comments on tempo button
2026-05-09 sketch out a tempo button
2026-05-09 have the engine handle the timer
    this moves physical timer peripheral management into Engine, which is
    where it should be. we now only use one timer to time everything.
    integrate physical buttons into the system
    also make Engine's initialization a bit more sane.
    - [in-progress] work on button
    - [in-progress] move plumbing to engine
2026-05-09 have the engine handle the timer (#15)
    this is a combination of two commits:
    - one timer peripheral, engine handles all the shit, sketches of pins to
    use
    - draft of a tap-tempo button, dunno if it works yet but relies on the
    new interface
2026-05-09 Multi-segment CIE interpolation
    As suggested by nausicaa
2026-05-09 Add a mock Led class for unit tests
    Via sufficient ifdef twiddling, make it so we can refer to LEDs in
    unit-test-only code, without relying on the existence of the HAL.
2026-05-09 Also add a mock LED controller
    Add a mock LED controller for unit tests too, since we're going to be
    referencing the LED controller in the UI
2026-05-09 Color constructors are constexpr
    They just are!
2026-05-09 write a circular array (buffer::Loop)
2026-05-09 address PR comments
2026-05-09 std::sort it
2026-05-09 rename: buffer::Loop -> buffer::CircularArray, Sample -> T
2026-05-09 write a circular array (`jazz::buffer::Loop`) (#16)
    two considerations:
    - i like fanciful names and all, but v willing to rename this
    `buffer::CircularBuffer` or smth for absolute clarity
    - division / modulo is bad. maybe we just make this always a
    power-of-two in length and use bitmasks for indexing?
2026-05-09 Add a KnobWithDisplay class
    Add a KnobWithDisplay class, which ties together the Knob
    class (tracking the current value of a knob) and a pluggable
    ValueDisplay class (which displays the current value using an RGB LED).
    This comes with a unit test (yay!) of the UI using this for a single
    parameter, just to demo it; later, we can update *all* the parameters to
    include some form of value display (probably with some deduplication, if
2026-05-09 enfore style guide on some stuff i just wrote
2026-05-09 enforce style guide on some stuff i just wrote (#19)
2026-05-24 Break Color namespace out into libjazz
    This is generally useful, not fridge-specific, so belongs in libjazz
    now.
2026-06-04 hard fautl
2026-06-04 no lfo :(
2026-06-04 wub wub
2026-06-13 Start to populate real pedal
    including the demo.toml preset, in config
2026-06-13 Fix O(n) append to updates
2026-06-13 Some integration between knobs and display
2026-06-13 Drop MemberCallback
    it's UB
2026-06-13 Global engine, initialized at startup
2026-06-13 Make ticks uint32
2026-06-13 Introduce an explicit Samples class
    to avoid confusion about what unit we were talking about
2026-06-13 Don't mutate root config
2026-06-13 1 head 1 lfo
2026-06-13 a preset that work?
2026-06-13 Impose style guide on transform::state
2026-06-13 Address a stale TODO
2026-06-13 Set up fuzztest
2026-06-13 Add a fuzz test for the sound engine
    This tests that any valid config, and any sequence of samples, never
    crashes the sound engine.
    It's currently failing! But for some reason the regression test doesn't
    reproduce that; I'll have to investigate more.
2026-06-13 make fmt
2026-06-13 Clean up config_transform a bit.
2026-06-16 slab: Add an IsFull method
2026-06-18 Readability nit in lfo.cpp
2026-06-18 Add a test that *dynamic* config also never crashes.
    A version of the existing fuzz test, but which also has the ability
    to *change* the config dynamically as samples are being fed in.
2026-06-19 add touch to console
2026-06-19 write an IIR filter
2026-06-19 implement IIR filter as direct form II transpose
2026-06-19 "it sounds fucking sick"
2026-06-19 add output filter, fix the NaNs
2026-06-20 docs: add datasheet for cd4051
2026-06-20 fridge/ui: Make knobs structs, not arrays
    Makes things a few notches more readable at construction time
2026-06-20 fridge/engine: Start to initialize real life pins again
2026-06-20 fridge/board: Lay down parts for a devboard
    Nothing is connected yet, and we're missing lots of things, but this is
    the bones of the part list
2026-06-20 fridge/ui: LFO range is of type Position
2026-06-20 ui: Own config, initialize at startup
    Initialize the config for the UI at startup, and have the UI own the
    config rather than it being a standalone global. Select both head and
    lfo 0 at startup, so that the initial value tracked by the knob matches
    the initial config.
    This works! and turning knobs changes parameters!
2026-06-21 fridge/led: break size of frame page into a variable
    Also comment to explain it, and fix an off-by-one bug with the
    zero-initialization.
2026-06-21 Disable release builds
    i2c doesn't work in release build. why? no idea. nothing good, I'm sure.
2026-06-21 Real pins for feedback LED
2026-06-21 fridge/value_display: BlackToWhite
    Super simple, tests that all the LEDs work
2026-06-21 engine: Fix address pins for muxen
2026-06-21 engine: there are 8 channels, not num muxes channels
2026-06-21 ui: Special Knob class for Feedback
    It displays as two interpolations, one from black to green (for read
    feedback) and one from black to red (for erase feedback).
2026-06-21 fridge: Avoid a couple memcpys
    I hate C++
